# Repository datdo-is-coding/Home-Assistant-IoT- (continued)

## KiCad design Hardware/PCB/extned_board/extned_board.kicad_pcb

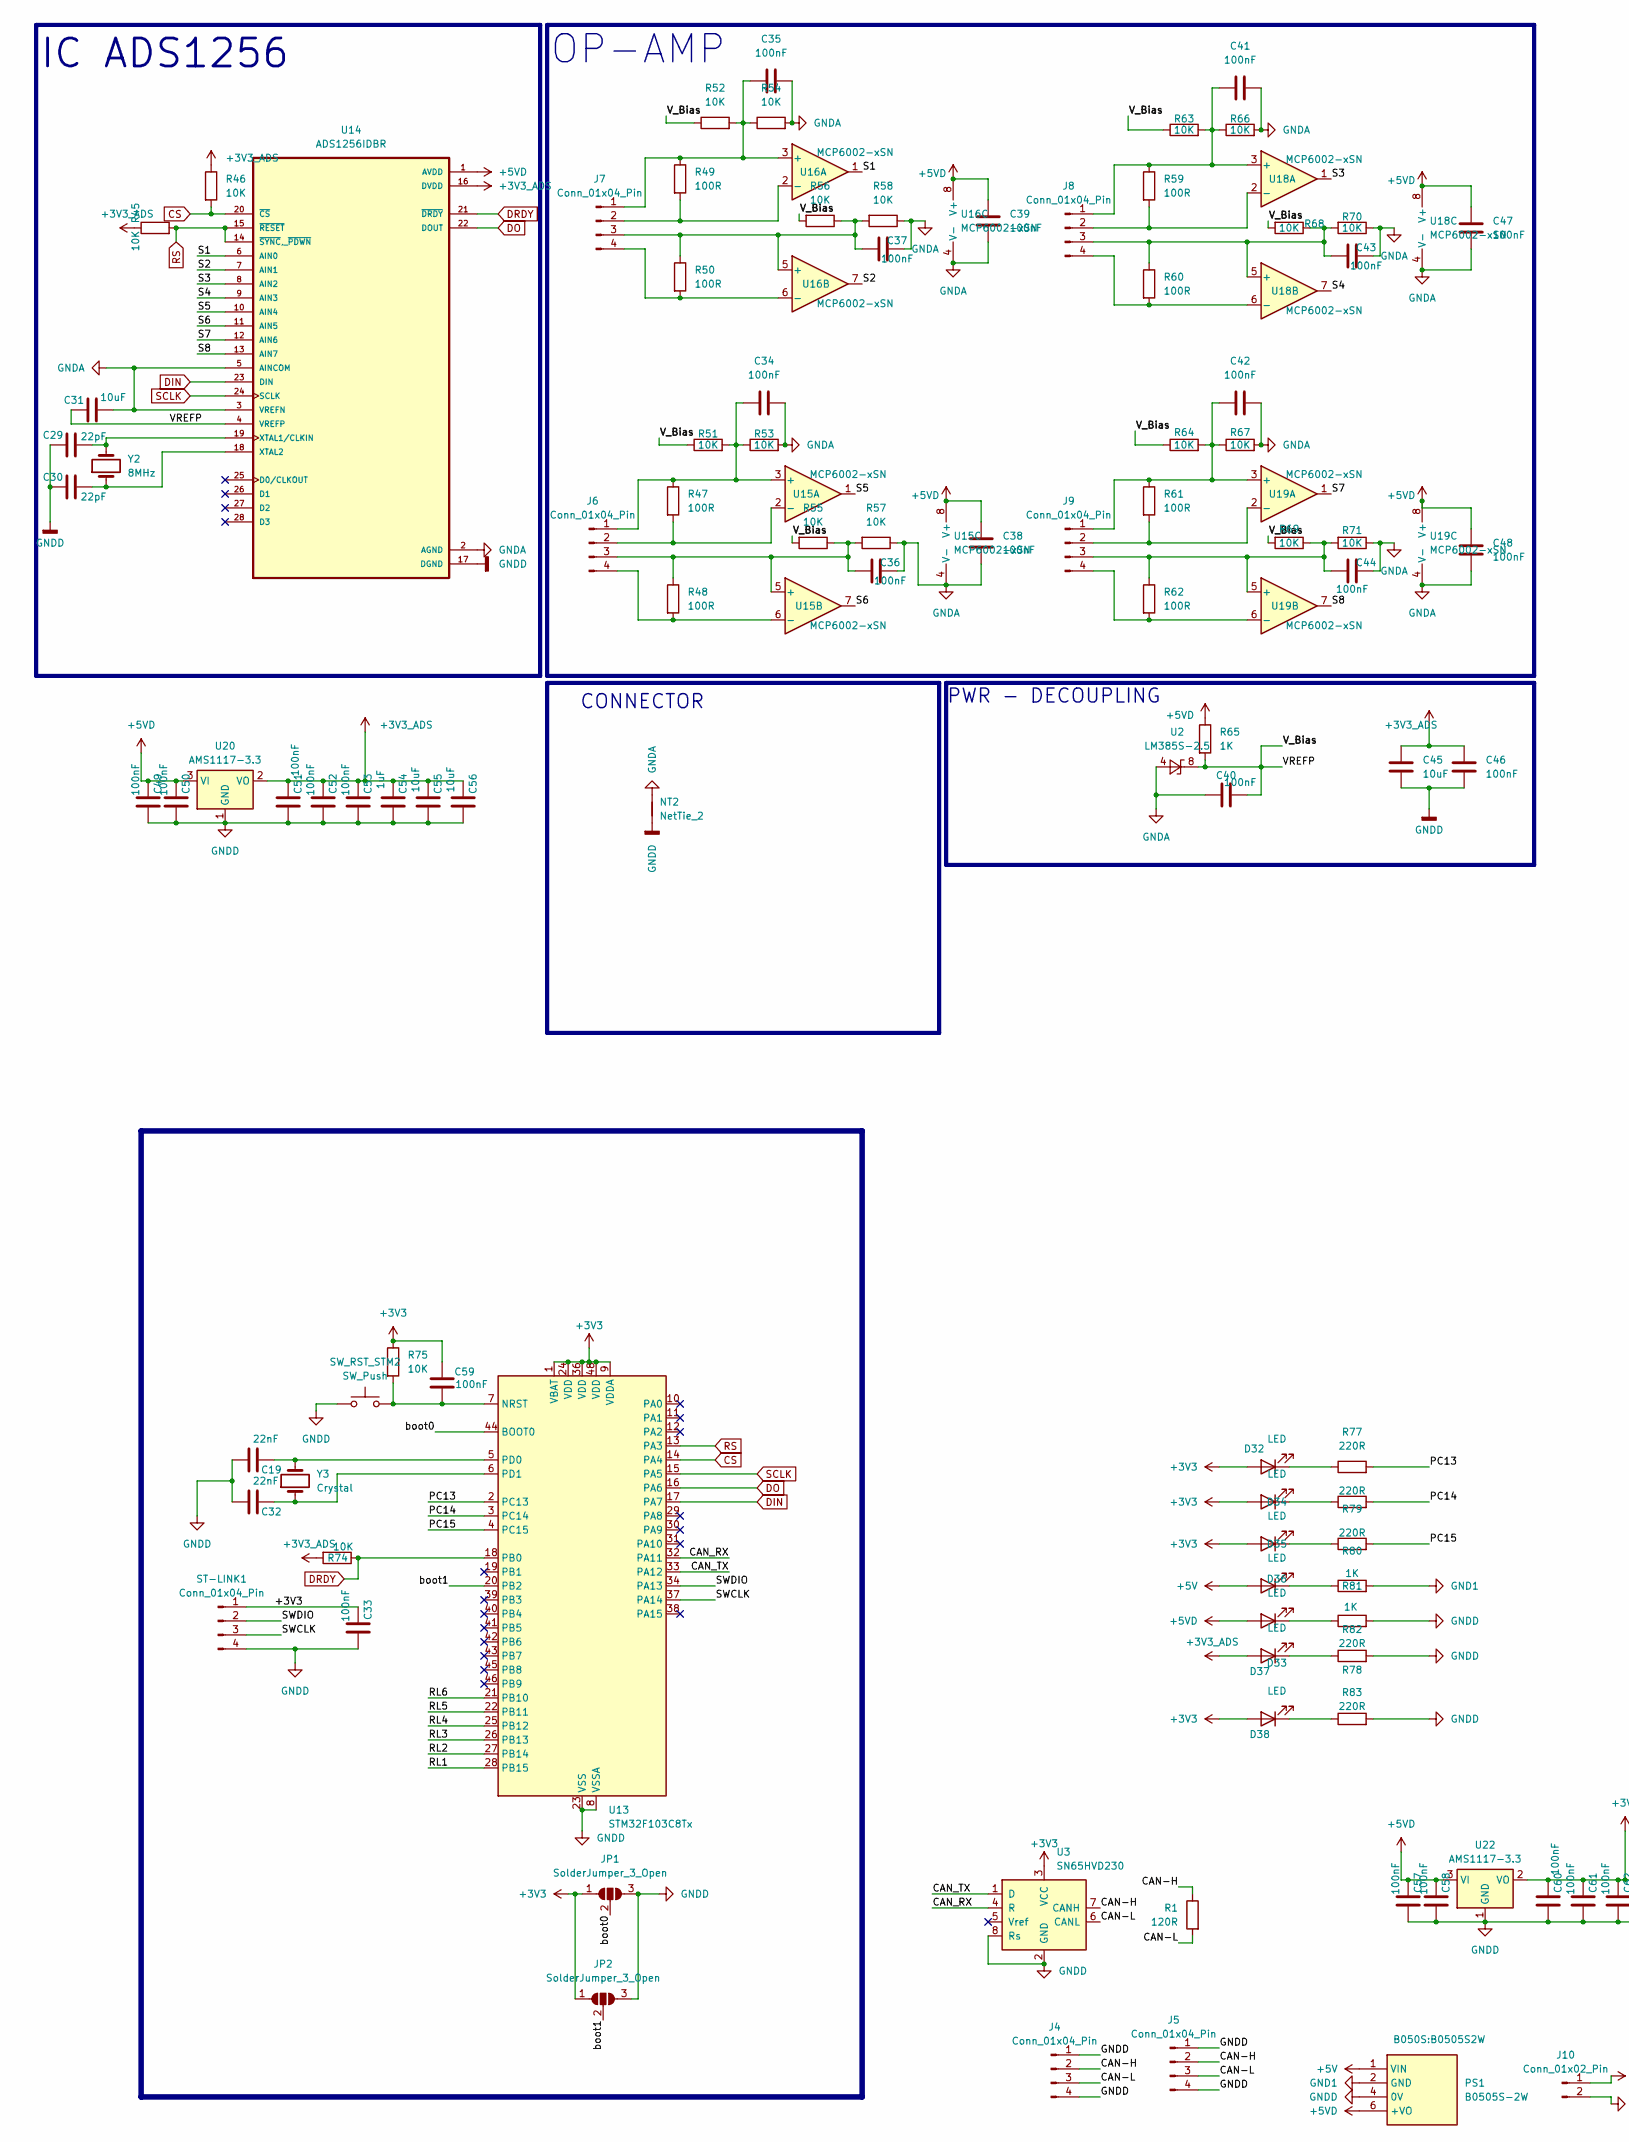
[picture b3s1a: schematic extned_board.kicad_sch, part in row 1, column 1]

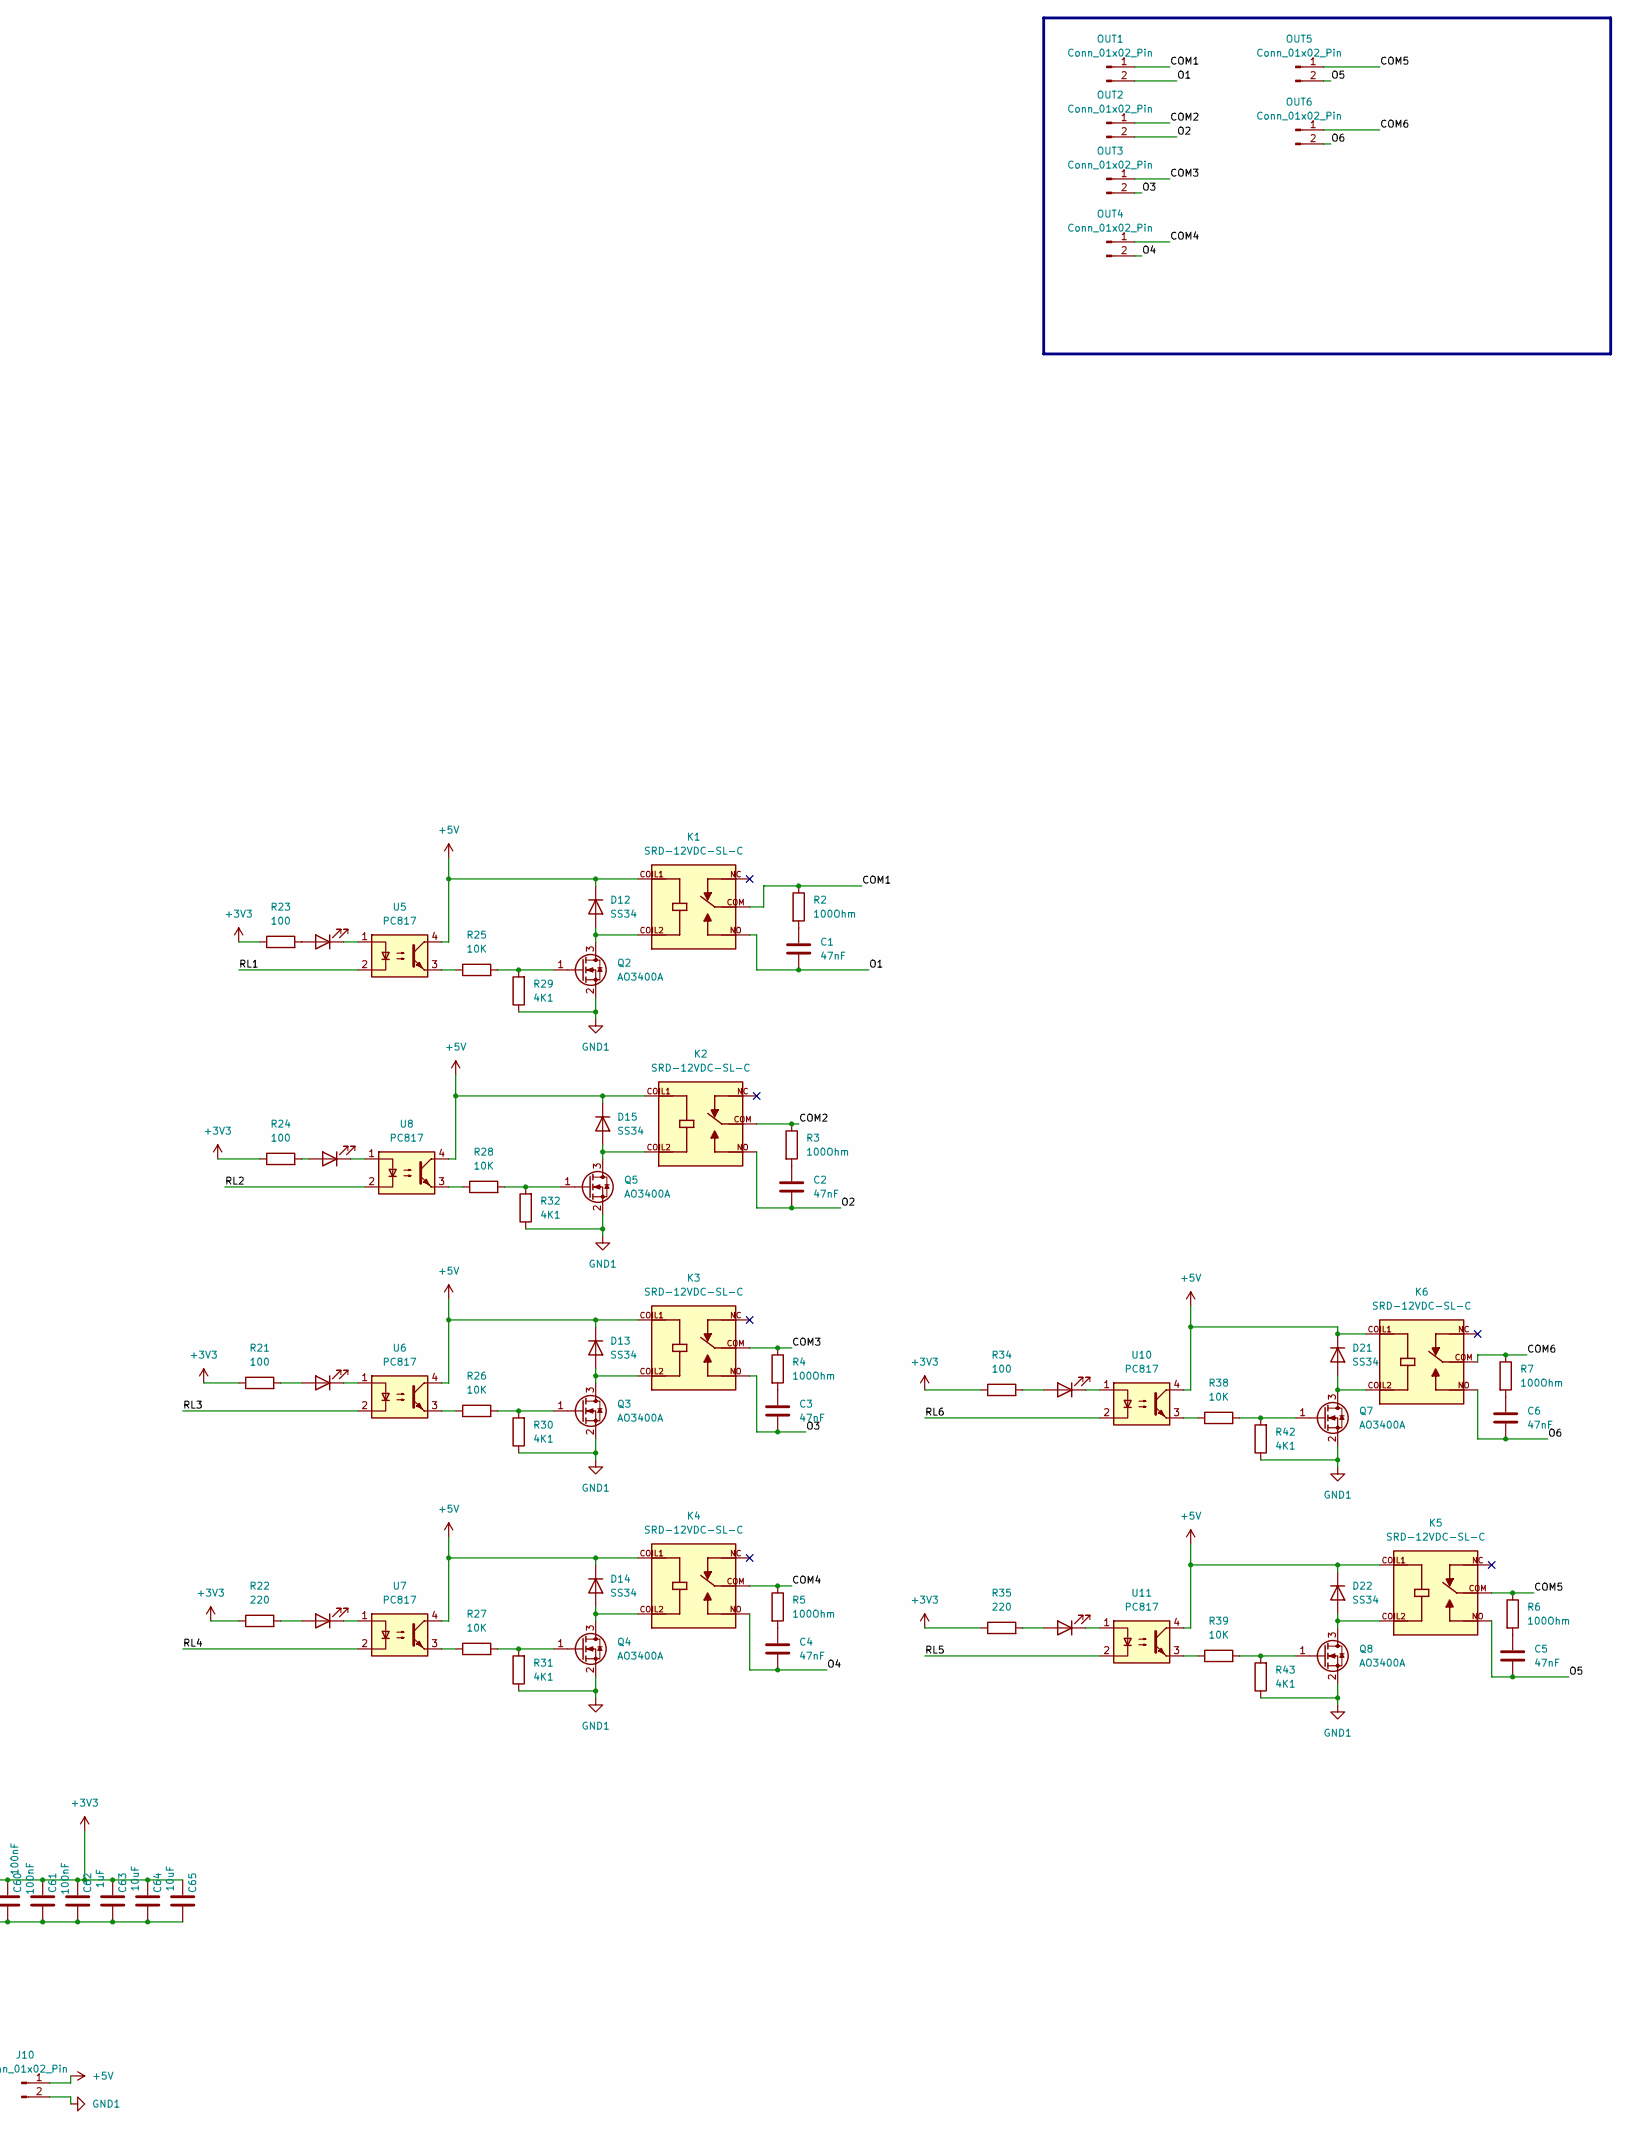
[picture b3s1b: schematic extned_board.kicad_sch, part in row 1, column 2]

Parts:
C1, C2, C3, C4, C5, C6: 47nF; C_Disc_D10.5mm_W5.0mm_P7.50mm
C19, C32: 22nF; R_0805_2012Metric_Pad1.20x1.40mm_HandSolder
C29, C30: 22pF; R_0805_2012Metric_Pad1.20x1.40mm_HandSolder
C31, C45, C55, C56, C64, C65: 10uF; R_0805_2012Metric_Pad1.20x1.40mm_HandSolder
C33, C34, C35, C36, C37, C38, C39, C40, C41, C42, C43, C44, C46, C47, C48, C49, C50, C51, C52, C53, C57, C58, C59, C60, C61, C62: 100nF; R_0805_2012Metric_Pad1.20x1.40mm_HandSolder
C54, C63: 1uF; R_0805_2012Metric_Pad1.20x1.40mm_HandSolder
D8, D9, D10, D11, D17, D18, D32, D33, D34, D35, D36, D37, D38: LED; LED_0805_2012Metric_Pad1.15x1.40mm_HandSolder
D12, D13, D14, D15, D21, D22: SS34; D_SMA_Handsoldering
J4, J5, J6, J7, J8, J9: Conn_01x04_Pin; PinHeader_1x04_P2.54mm_Vertical
J10: Conn_01x02_Pin; PinHeader_1x02_P2.54mm_Vertical
JP1, JP2: SolderJumper_3_Open; SolderJumper-3_P1.3mm_Open_RoundedPad1.0x1.5mm_NumberLabels
K1, K2, K3, K4, K5, K6: SRD-12VDC-SL-C; RELAY_SRD-12VDC-SL-C; PARTREV 1.0
NT2: NetTie_2; NetTie-2_THT_Pad0.3mm
OUT1, OUT2, OUT3, OUT4, OUT5, OUT6: Conn_01x02_Pin; 2P
PS1: B0505S-2W; B0505S2W; Manufacturer_Part_Number B0505S-2W
Q2, Q3, Q4, Q5, Q7, Q8: AO3400A; SOT-23
R1: 120R; R_0805_2012Metric_Pad1.20x1.40mm_HandSolder
R2, R3, R4, R5, R6, R7: 100Ohm; R_Axial_DIN0414_L11.9mm_D4.5mm_P15.24mm_Horizontal
R21, R23, R24, R34: 100; R_0805_2012Metric_Pad1.20x1.40mm_HandSolder
R22, R35: 220; R_0805_2012Metric_Pad1.20x1.40mm_HandSolder
R25, R26, R27, R28, R38, R39, R45, R46, R51, R52, R53, R54, R55, R56, R57, R58, R63, R64, R66, R67, R68, R69, R70, R71, R74, R75: 10K; R_0805_2012Metric_Pad1.20x1.40mm_HandSolder
R29, R30, R31, R32, R42, R43: 4K1; R_0805_2012Metric_Pad1.20x1.40mm_HandSolder
R47, R48, R49, R50, R59, R60, R61, R62: 100R; R_0805_2012Metric_Pad1.20x1.40mm_HandSolder
R65, R80, R81: 1K; R_0805_2012Metric_Pad1.20x1.40mm_HandSolder
R77, R78, R79, R82, R83: 220R; R_0805_2012Metric_Pad1.20x1.40mm_HandSolder
ST-LINK1: Conn_01x04_Pin; PinHeader_1x04_P2.54mm_Vertical
SW_RST_STM2: SW_Push; SW_SPST_FSMSM
U2: LM385S-2.5; SOIC-8_3.9x4.9mm_P1.27mm
U3: SN65HVD230; SOIC-8_3.9x4.9mm_P1.27mm
U5, U6, U7, U8, U10, U11: PC817; DIL04
U13: STM32F103C8Tx; LQFP-48_7x7mm_P0.5mm
U14: ADS1256IDBR; SOP65P780X200-28N
U15, U16, U18, U19: MCP6002-xSN; SOIC8-N_MC_MCH-M
U20, U22: AMS1117-3.3; SOT-223-3_TabPin2
Y2: 8MHz; Resonator-2Pin_W7.0mm_H2.5mm
Y3: Crystal; Resonator-2Pin_W7.0mm_H2.5mm

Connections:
+3V3: C33.2, C59.2, C60.2, C61.2, C62.2, C63.2, C64.2, C65.2, D32.2 (A), D33.2 (A), D34.2 (A), D38.2 (A), JP1.1 (A), JP2.1 (A), R21.1, R22.1, R23.1, R24.1, R34.1, R35.1, R75.1, ST-LINK1.1, U3.3 (VCC), U13.1 (VBAT), U13.9 (VDDA), U13.24 (VDD), U13.36 (VDD), U13.48 (VDD), U22.2 (VO); also elsewhere on the board
+3V3_ADS: C45.1, C46.1, C51.2, C52.2, C53.2, C54.2, C55.2, C56.2, D37.2 (A), R45.1, R46.1, R74.2, U14.16 (DVDD), U20.2 (VO)
+5V: D12.1 (K), D13.1 (K), D14.1 (K), D15.1 (K), D21.1 (K), D22.1 (K), D35.2 (A), J10.1, K1.COIL1, K2.COIL1, K3.COIL1, K4.COIL1, K5.COIL1, K6.COIL1, PS1.1 (VIN), U5.4, U6.4, U7.4, U8.4, U10.4, U11.4
+5VD: C38.1, C39.1, C47.1, C48.1, C49.2, C50.2, C57.2, C58.2, D36.2 (A), PS1.6 (+VO), R65.1, U14.1 (AVDD), U15.8 (V+), U16.8 (V+), U18.8 (V+), U19.8 (V+), U20.3 (VI), U22.3 (VI)
/CAN-H: J4.2, J5.2, R1.1, U3.7 (CANH); also elsewhere on the board
/CAN-L: J4.3, J5.3, R1.2, U3.6 (CANL); also elsewhere on the board
/CAN_RX: U3.4 (R), U13.32 (PA11)
/CAN_TX: U3.1 (D), U13.33 (PA12)
/COM1: K1.COM, OUT1.1, R2.1
/COM2: K2.COM, OUT2.1, R3.1
/COM3: K3.COM, OUT3.1, R4.1
/COM4: K4.COM, OUT4.1, R5.1
/COM5: K5.COM, OUT5.1, R6.1
/COM6: K6.COM, OUT6.1, R7.1
/O1: C1.2, K1.NO, OUT1.2
/O2: C2.2, K2.NO, OUT2.2
/O3: C3.2, K3.NO, OUT3.2
/O4: C4.2, K4.NO, OUT4.2
/O5: C5.2, K5.NO, OUT5.2
/O6: C6.2, K6.NO, OUT6.2
/PC13: R77.2, U13.2 (PC13)
/PC14: R78.2, U13.3 (PC14)
/PC15: R79.2, U13.4 (PC15)
/RL1: U5.2, U13.28 (PB15)
/RL2: U8.2, U13.27 (PB14)
/RL3: U6.2, U13.26 (PB13)
/RL4: U7.2, U13.25 (PB12)
/RL5: U11.2, U13.22 (PB11)
/RL6: U10.2, U13.21 (PB10)
/S1: U14.6 (AIN0), U16.1
/S2: U14.7 (AIN1), U16.7
/S3: U14.8 (AIN2), U18.1
/S4: U14.9 (AIN3), U18.7
/S5: U14.10 (AIN4), U15.1
/S6: U14.11 (AIN5), U15.7
/S7: U14.12 (AIN6), U19.1
/S8: U14.13 (AIN7), U19.7
/SWCLK: ST-LINK1.3, U13.37 (PA14); also elsewhere on the board
/SWDIO: ST-LINK1.2, U13.34 (PA13); also elsewhere on the board
/VREFP: C31.2, C40.1, R51.1, R52.1, R55.2, R56.2, R63.1, R64.1, R65.2, R68.2, R69.2, U2.6 (K), U2.8 (K), U14.4 (VREFP)
/boot0: JP1.2 (C), U13.44 (BOOT0)
/boot1: JP2.2 (C), U13.20 (PB2)
CS: R46.2, U13.14 (PA4), U14.20 (~CS)
DIN: U13.17 (PA7), U14.23 (DIN)
DO: U13.16 (PA6), U14.22 (DOUT)
DRDY: R74.1, U13.18 (PB0), U14.21 (~DRDY)
GND1: J10.2, PS1.2 (GND), Q2.2 (S), Q3.2 (S), Q4.2 (S), Q5.2 (S), Q7.2 (S), Q8.2 (S), R29.1, R30.1, R31.1, R32.1, R42.1, R43.1, R80.2
GNDA: C31.1, C34.2, C35.2, C36.2, C37.2, C38.2, C39.2, C40.2, C41.2, C42.2, C43.2, C44.2, C47.2, C48.2, NT2.2, R53.2, R54.2, R57.1, R58.1, R66.2, R67.2, R70.1, R71.1, U2.4 (A), U14.2 (AGND), U14.3 (VREFN), U14.5 (AINCOM), U15.4 (V-), U16.4 (V-), U18.4 (V-), U19.4 (V-)
GNDD: C19.1, C29.2, C30.2, C32.1, C33.1, C45.2, C46.2, C49.1, C50.1, C51.1, C52.1, C53.1, C54.1, C55.1, C56.1, C57.1, C58.1, C60.1, C61.1, C62.1, C63.1, C64.1, C65.1, JP1.3 (B), JP2.3 (B), NT2.1, PS1.4 (0V), R81.2, R82.2, R83.2, ST-LINK1.4, SW_RST_STM2.1, U3.2 (GND), U3.8 (Rs), U13.8 (VSSA), U13.23 (VSS), U13.35 (VSS), U13.47 (VSS), U14.17 (DGND), U20.1 (GND), U22.1 (GND); also elsewhere on the board
unnamed: C1.1, R2.2
unnamed: C2.1, R3.2
unnamed: C3.1, R4.2
unnamed: C4.1, R5.2
unnamed: C5.1, R6.2
unnamed: C6.1, R7.2
unnamed: D8.2 (A), R23.2
unnamed: D8.1 (K), U5.1
unnamed: D9.2 (A), R21.2
unnamed: D9.1 (K), U6.1
unnamed: D10.2 (A), R22.2
unnamed: D10.1 (K), U7.1
unnamed: D11.2 (A), R24.2
unnamed: D11.1 (K), U8.1
unnamed: D12.2 (A), K1.COIL2, Q2.3 (D)
unnamed: D13.2 (A), K3.COIL2, Q3.3 (D)
unnamed: D14.2 (A), K4.COIL2, Q4.3 (D)
unnamed: D15.2 (A), K2.COIL2, Q5.3 (D)
unnamed: D17.2 (A), R34.2
unnamed: D17.1 (K), U10.1
unnamed: D18.2 (A), R35.2
unnamed: D18.1 (K), U11.1
unnamed: D21.2 (A), K6.COIL2, Q7.3 (D)
unnamed: D22.2 (A), K5.COIL2, Q8.3 (D)
unnamed: D32.1 (K), R77.1
unnamed: D33.1 (K), R78.1
unnamed: D34.1 (K), R79.1
unnamed: D35.1 (K), R80.1
unnamed: D36.1 (K), R81.1
unnamed: D37.1 (K), R82.1
unnamed: D38.1 (K), R83.1
unnamed: J4.1, J4.4, J5.1, J5.4
unnamed: C34.1, J6.1, R47.1, R51.2, R53.1, U15.3 (+)
unnamed: J6.2, R47.2, U15.2 (-)
unnamed: C36.1, J6.3, R48.1, R55.1, R57.2, U15.5 (+)
unnamed: J6.4, R48.2, U15.6 (-)
unnamed: C35.1, J7.1, R49.1, R52.2, R54.1, U16.3 (+)
unnamed: J7.2, R49.2, U16.2 (-)
unnamed: C37.1, J7.3, R50.1, R56.1, R58.2, U16.5 (+)
unnamed: J7.4, R50.2, U16.6 (-)
unnamed: C41.1, J8.1, R59.1, R63.2, R66.1, U18.3 (+)
unnamed: J8.2, R59.2, U18.2 (-)
unnamed: C43.1, J8.3, R60.1, R68.1, R70.2, U18.5 (+)
unnamed: J8.4, R60.2, U18.6 (-)
unnamed: C42.1, J9.1, R61.1, R64.2, R67.1, U19.3 (+)
unnamed: J9.2, R61.2, U19.2 (-)
unnamed: C44.1, J9.3, R62.1, R69.1, R71.2, U19.5 (+)
unnamed: J9.4, R62.2, U19.6 (-)
unnamed: Q2.1 (G), R25.2, R29.2
unnamed: Q3.1 (G), R26.2, R30.2
unnamed: Q4.1 (G), R27.2, R31.2
unnamed: Q5.1 (G), R28.2, R32.2
unnamed: Q7.1 (G), R38.2, R42.2
unnamed: Q8.1 (G), R39.2, R43.2
unnamed: R25.1, U5.3
unnamed: R26.1, U6.3
unnamed: R27.1, U7.3
unnamed: R28.1, U8.3
unnamed: R38.1, U10.3
unnamed: R39.1, U11.3
unnamed 109: C59.1, R75.2, SW_RST_STM2.2, U13.7 (NRST); also elsewhere on the board
unnamed: C19.2, U13.5 (PD0), Y3.2
unnamed: C32.2, U13.6 (PD1), Y3.1
unnamed: C29.1, U14.19 (XTAL1/CLKIN), Y2.2
unnamed: C30.1, U14.18 (XTAL2), Y2.1
RS: R45.2, U13.13 (PA3), U14.14 (~SYNC,_~PDWN), U14.15 (~RESET)
SCLK: U13.15 (PA5), U14.24 (SCLK)

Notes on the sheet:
PWR - DECOUPLING
OP-AMP
IC ADS1256
CONNECTOR

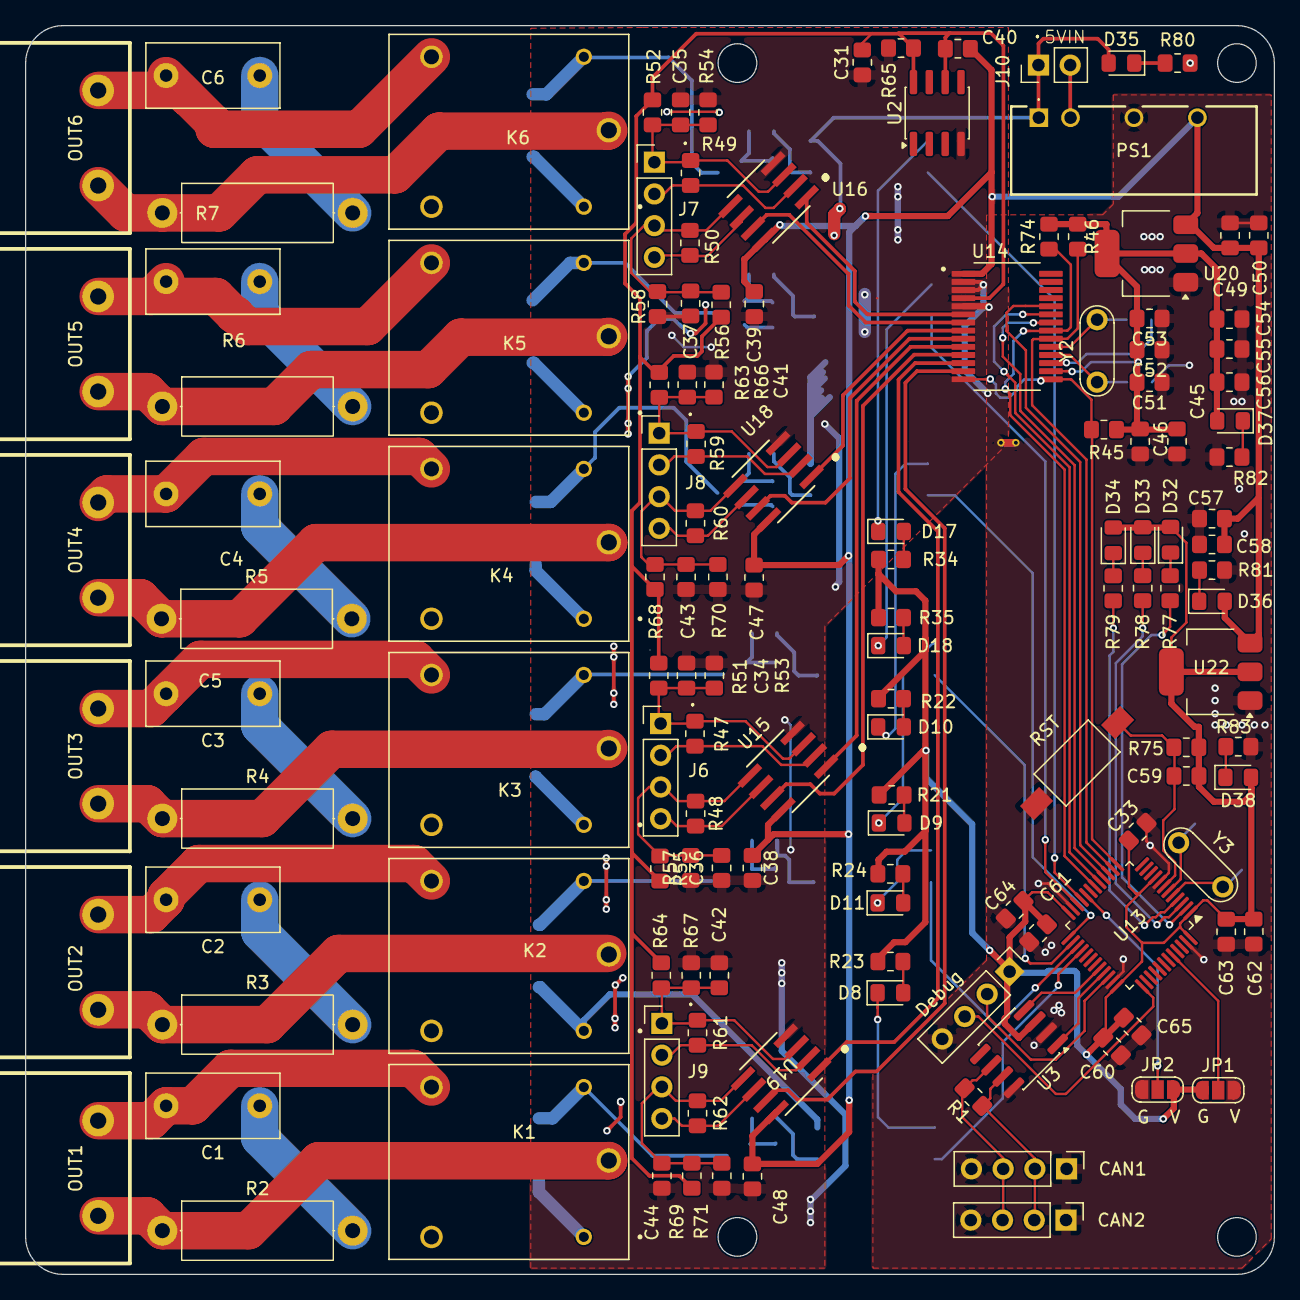
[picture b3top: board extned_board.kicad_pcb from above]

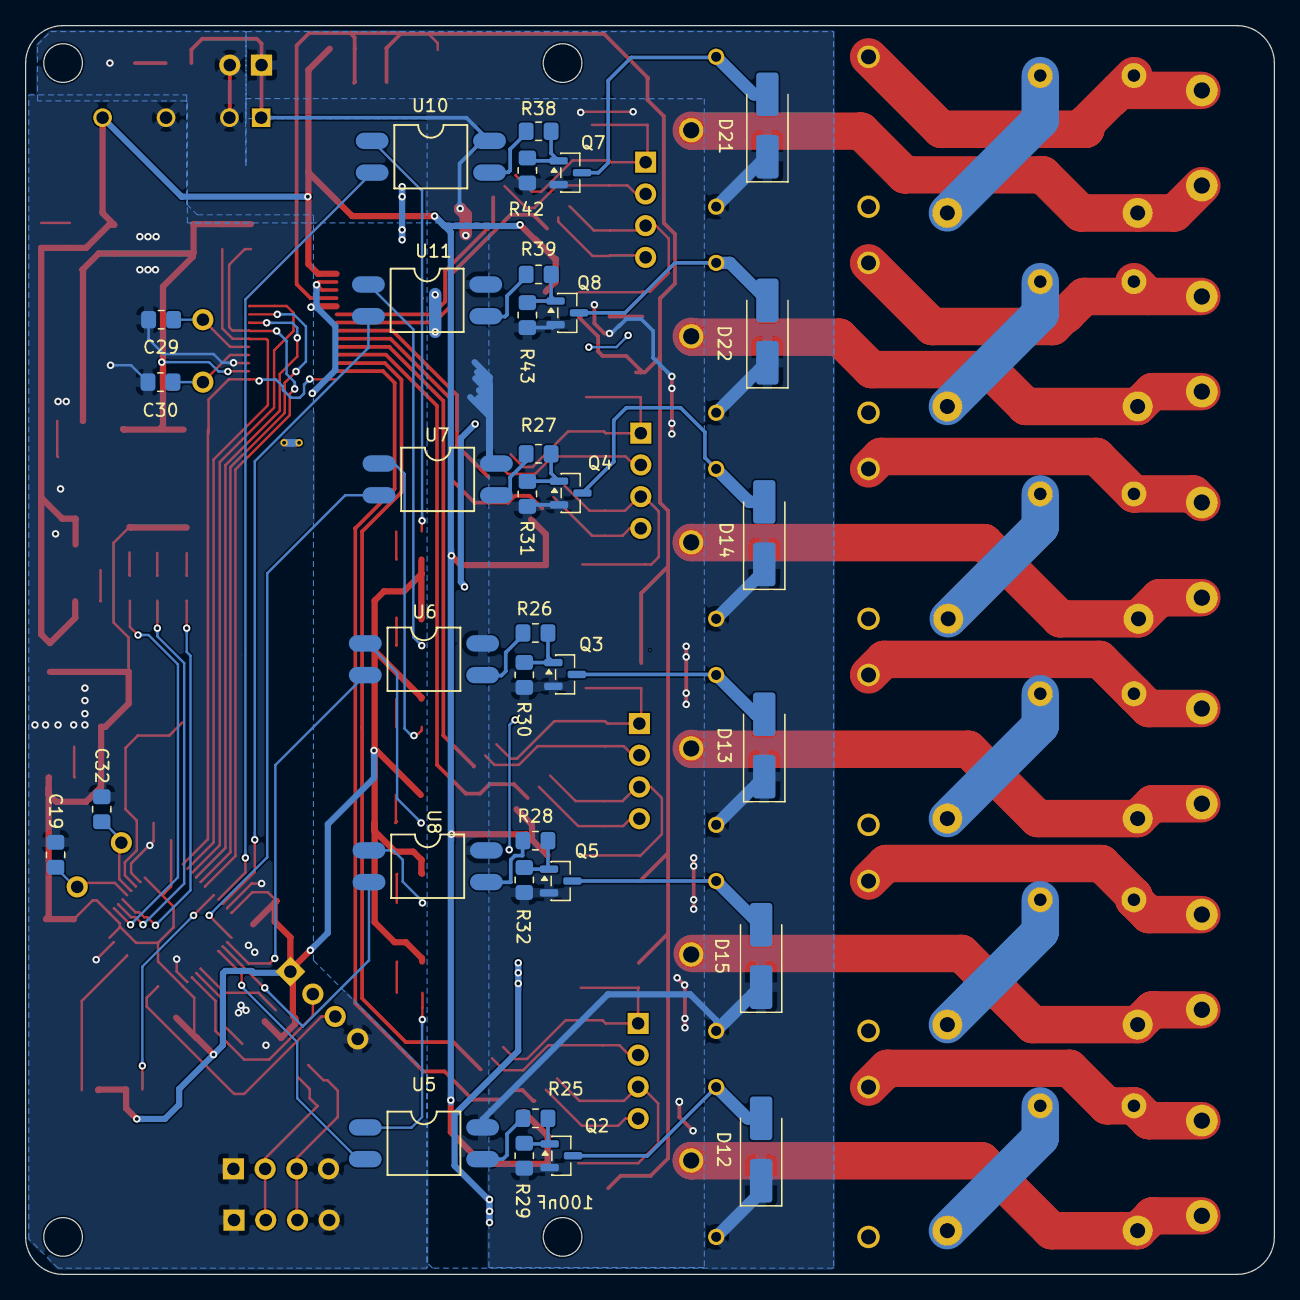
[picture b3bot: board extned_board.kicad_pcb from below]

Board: 2 copper layers, 100.0 x 100.0 mm, 173 parts (34 on the bottom side), 115 nets.

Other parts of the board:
CAN1, CAN2: Conn_01x04_Pin; PinHeader_1x04_P2.54mm_Vertical
Debug: Conn_01x04_Pin; PinHeader_1x04_P2.54mm_Vertical
RST: SW_Push; SW_SPST_FSMSM

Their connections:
+3V3: Debug.1; also elsewhere on the board
/CAN-H: CAN1.2, CAN2.2; also elsewhere on the board
/CAN-L: CAN1.3, CAN2.3; also elsewhere on the board
/SWCLK: Debug.3; also elsewhere on the board
/SWDIO: Debug.2; also elsewhere on the board
GNDD: CAN1.1, CAN1.4, CAN2.1, CAN2.4, Debug.4, RST.1; also elsewhere on the board
unnamed 109: RST.2; also elsewhere on the board

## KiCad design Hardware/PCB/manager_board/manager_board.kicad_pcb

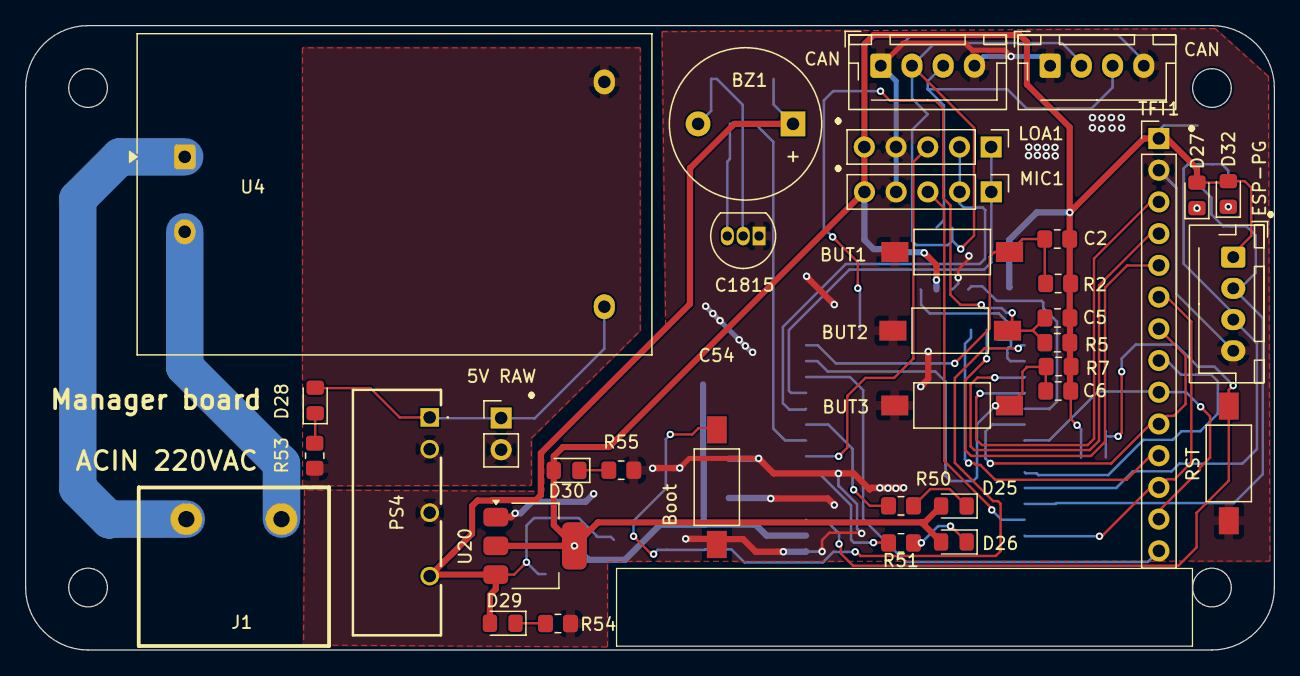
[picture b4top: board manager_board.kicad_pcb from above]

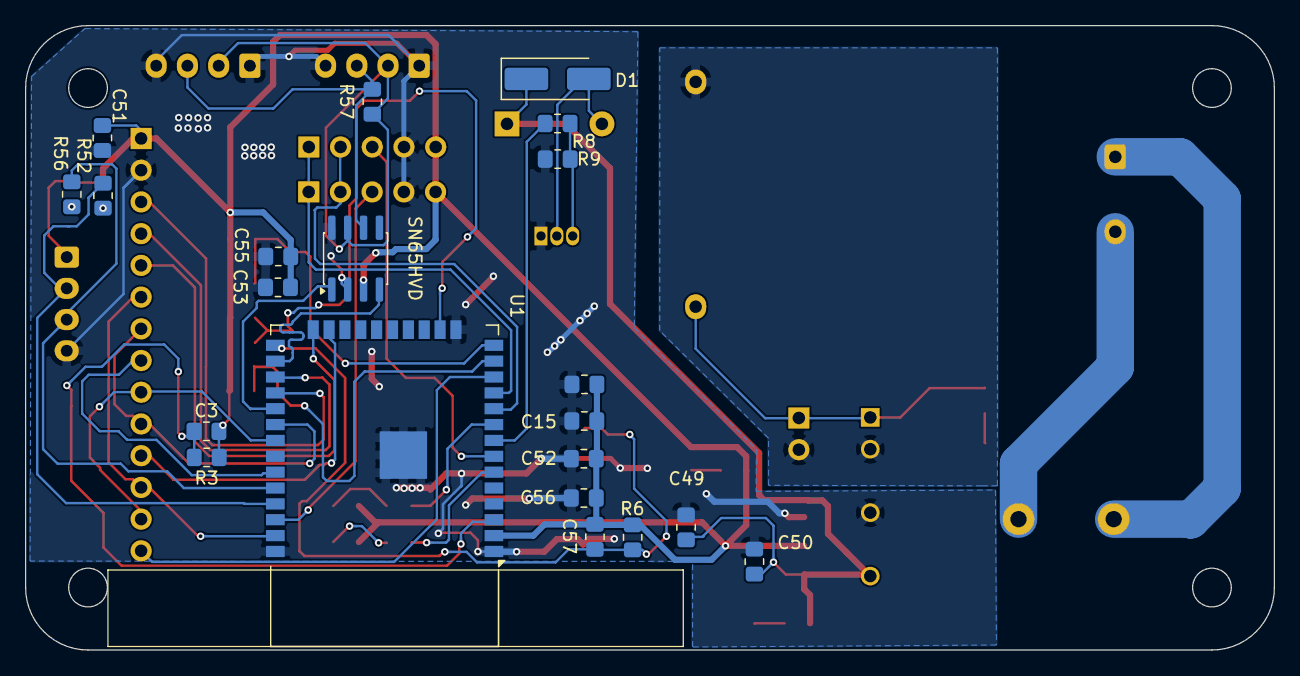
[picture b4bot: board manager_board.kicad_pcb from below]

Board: 2 copper layers, 100.0 x 50.0 mm, 57 parts (21 on the bottom side), 43 nets.

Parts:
5V RAW: Conn_01x02_Pin; PinHeader_1x02_P2.54mm_Vertical
BUT1, BUT2, BUT3: SW_Push; SW_SPST_FSMSM
BZ1: Buzzer; Buzzer_12x9.5RM7.6
Boot: SW_Push; SW_SPST_FSMSM
C2, C3, C5, C6, C49, C50, C51, C52, C53, C57: 100nF; R_0805_2012Metric_Pad1.20x1.40mm_HandSolder
C15, C55, C56: 10uF; R_0805_2012Metric_Pad1.20x1.40mm_HandSolder
C54: 1uF; R_0805_2012Metric_Pad1.20x1.40mm_HandSolder
C1815: 2SC1815; TO-92_Inline
CAN: Conn_01x04_Pin; JST_XH_B4B-XH-AM_1x04_P2.50mm_Vertical
CAN#2: Conn_01x04_Pin; JST_XH_B4B-XH-AM_1x04_P2.50mm_Vertical
D1: 1N4007; D_SMA_Handsoldering
D25, D26, D27, D28, D29, D30, D32: LED; LED_0805_2012Metric_Pad1.15x1.40mm_HandSolder
ESP-PG: Conn_01x04_Pin; JST_XH_B4B-XH-AM_1x04_P2.50mm_Vertical
J1: KF7.62-2P; 2P
LOA1: Conn_01x05_Pin; PinHeader_1x05_P2.54mm_Vertical
MIC1: Conn_01x05_Pin; PinHeader_1x05_P2.54mm_Vertical
PS4: B0505S-2W; B0505S2W
R2, R3, R5, R6, R7, R9: 10K; R_0805_2012Metric_Pad1.20x1.40mm_HandSolder
R8, R52, R53, R54, R56: 1K; R_0805_2012Metric_Pad1.20x1.40mm_HandSolder
R50, R51, R55: 220R; R_0805_2012Metric_Pad1.20x1.40mm_HandSolder
R57: 120R; R_0805_2012Metric_Pad1.20x1.40mm_HandSolder
RST: SW_Push; SW_SPST_FSMSM
SN65HVD: SN65HVD230; SOIC-8_3.9x4.9mm_P1.27mm
TFT1: Conn_01x14_Pin; PinHeader_1x14_P2.54mm_Vertical
U1: ESP32-WROOM-32D
U4: HLK-5M05; Converter_ACDC_Hi-Link_HLK-5Mxx
U20: AMS1117-3.3; SOT-223-3_TabPin2

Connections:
+3V3_ESP: C2.2, C3.2, C5.2, C6.2, C15.2, C51.2, C52.2, C53.2, C54.2, C55.2, C56.2, C57.2, D25.2 (A), D26.2 (A), D27.2 (A), D30.2 (A), D32.2 (A), ESP-PG.1, LOA1.5, MIC1.5, R2.1, R3.1, R5.1, R6.1, R7.1, SN65HVD.3 (VCC), TFT1.1, U1.2 (VDD), U20.2 (VO)
+5V: 5V RAW.1, D28.2 (A), PS4.1 (VIN), U4.4 (+Vout)
+5VD1: BZ1.1 (+), C49.2, C50.2, D1.1 (K), D29.2 (A), PS4.6 (+VO), U20.3 (VI)
/BUT1: BUT1.2, C2.1, R2.2, U1.14 (IO12)
/BUT2: BUT2.2, C5.1, R5.2, U1.16 (IO13)
/BUT3: BUT3.2, C6.1, R7.2, U1.13 (IO14)
/CAN-H: CAN.2, CAN#2.2, R57.2, SN65HVD.7 (CANH)
/CAN-L: CAN.3, CAN#2.3, R57.1, SN65HVD.6 (CANL)
/CAN_RX: SN65HVD.4 (R), U1.26 (IO4)
/CAN_TX: SN65HVD.1 (D), U1.29 (IO5)
/I2S_BCLK: LOA1.1, MIC1.1, U1.11 (IO26)
/I2S_DIN: LOA1.3, U1.7 (IO35)
/I2S_DOUT: MIC1.3, U1.36 (IO22)
/I2S_WS: LOA1.2, MIC1.2, U1.10 (IO25)
/LED1: R50.2, U1.9 (IO33)
/LED2: R51.2, U1.6 (IO34)
/RX0: ESP-PG.3, R56.2, U1.34 (RXD0/IO3)
/TFT_CS: TFT1.3, U1.28 (IO17)
/TFT_DC: TFT1.5, U1.24 (IO2)
/TFT_LED: TFT1.8, U1.33 (IO21)
/TFT_MISO: TFT1.9, TFT1.13, U1.31 (IO19)
/TFT_MOSI: TFT1.6, TFT1.12, U1.37 (IO23)
/TFT_RS: TFT1.4, U1.27 (IO16)
/TFT_SCK: TFT1.7, TFT1.10, U1.30 (IO18)
/TO_CS: TFT1.11, U1.23 (IO15)
/TO_IRQ: TFT1.14, U1.12 (IO27)
/TX0: ESP-PG.2, R52.2, U1.35 (TXD0/IO1)
/buzz: R8.1, U1.8 (IO32)
GND1: 5V RAW.2, PS4.2 (GND), R53.2, U4.3 (-Vout)
GNDD: BUT1.1, BUT2.1, BUT3.1, Boot.2, C15.1, C49.1, C50.1, C51.1, C52.1, C53.1, C54.1, C55.1, C56.1, C1815.1 (E), CAN.1, CAN.4, CAN#2.1, CAN#2.4, ESP-PG.4, LOA1.4, MIC1.4, PS4.4 (0V), R9.2, R54.2, R55.2, RST.1, SN65HVD.2 (GND), SN65HVD.8 (Rs), TFT1.2, U1.1 (GND), U1.15 (GND), U1.38 (GND), U1.39 (GND), U20.1 (GND)
unnamed: BZ1.2 (-), C1815.2 (C), D1.2 (A)
unnamed: D25.1 (K), R50.1
unnamed: D26.1 (K), R51.1
unnamed: D27.1 (K), R52.1
unnamed: D28.1 (K), R53.1
unnamed: D29.1 (K), R54.1
unnamed: D30.1 (K), R55.1
unnamed: D32.1 (K), R56.1
unnamed: C1815.3 (B), R8.2, R9.1
unnamed: C3.1, R3.2, RST.2, U1.3 (EN)
unnamed: Boot.1, C57.1, R6.2, U1.25 (IO0)
unnamed: J1.2, U4.1 (AC/L)
unnamed: J1.1, U4.2 (AC/N)

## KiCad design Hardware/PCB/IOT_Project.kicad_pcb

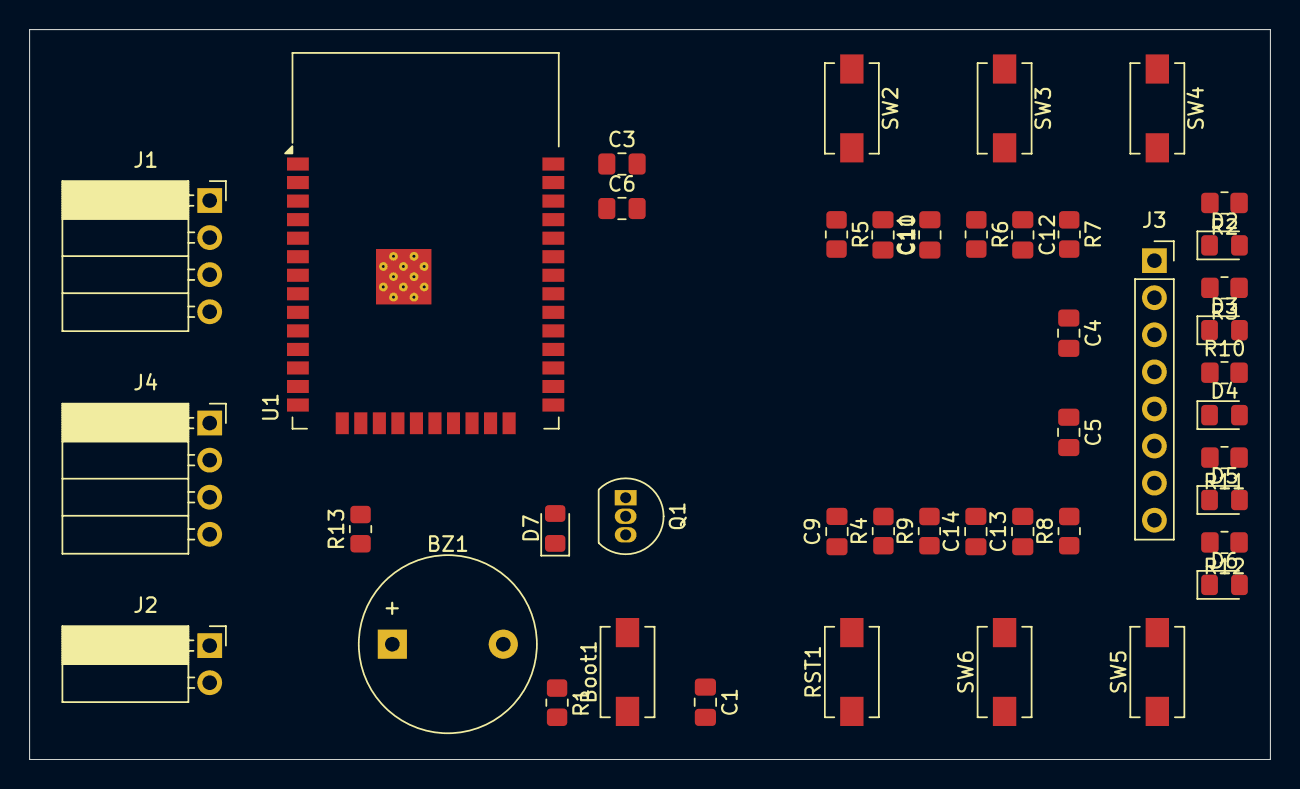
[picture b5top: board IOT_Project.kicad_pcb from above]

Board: 2 copper layers, 85.0 x 50.0 mm, 44 parts (0 on the bottom side), 31 nets, no tracks yet.

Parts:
BZ1: Buzzer; Buzzer_12x9.5RM7.6
Boot1: SW_Push; SW_SPST_EVQPE1
C1, C3, C4, C5, C6, C9, C10, C11, C12, C13, C14: 100nF; C_0805_2012Metric_Pad1.18x1.45mm_HandSolder
D2, D3, D4, D5, D6: LED; LED_0805_2012Metric_Pad1.15x1.40mm_HandSolder
D7: D; D_0805_2012Metric_Pad1.15x1.40mm_HandSolder
J1: Conn_01x04_Pin; PinSocket_1x04_P2.54mm_Horizontal
J2: POWER IN 3V3; PinSocket_1x02_P2.54mm_Horizontal
J3: TFT_2.4; PinSocket_1x08_P2.54mm_Vertical
J4: Program; PinSocket_1x04_P2.54mm_Horizontal
Q1: 2SC1815; TO-92_Inline
R1, R4, R5, R6, R7, R8, R9: 10K; R_0805_2012Metric_Pad1.20x1.40mm_HandSolder
R2, R3, R10, R11, R12: 330R; R_0805_2012Metric_Pad1.20x1.40mm_HandSolder
R13: 1K; R_0805_2012Metric_Pad1.20x1.40mm_HandSolder
RST1: SW_Push; SW_SPST_EVQPE1
SW2, SW3, SW4, SW5, SW6: SW_Push; SW_SPST_EVQPE1
U1: ESP32-WROOM-32D

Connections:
+3.3V: BZ1.1 (+), C3.1, C4.1, C5.1, C6.1, D7.1 (K), J1.1, J2.1, J3.1, J4.1, R1.2, R2.2, R3.2, R4.2, R5.2, R6.2, R7.2, R8.2, R9.2, R10.2, R11.2, R12.2, U1.2 (VDD)
BL: J3.8, U1.8 (IO32)
BOOT: Boot1.2, C1.1, R1.1, U1.25 (IO0)
BUT1: C10.1, R5.1, SW2.2, U1.9 (IO33)
BUT2: C11.1, R6.1, SW3.2, U1.6 (IO34)
BUT3: C12.1, R7.1, SW4.2, U1.7 (IO35)
BUT4: C13.1, R8.1, SW5.2, U1.4 (SENSOR_VP)
BUT5: C14.1, R9.1, SW6.2, U1.5 (SENSOR_VN)
Buzz: R13.2, U1.16 (IO13)
CLK: J3.7, U1.30 (IO18)
CS: J3.3, U1.29 (IO5)
DC: J3.5, U1.26 (IO4)
GND: Boot1.1, C1.2, C3.2, C4.2, C5.2, C6.2, C9.2, C10.2, C11.2, C12.2, C13.2, C14.2, D2.1 (K), J1.4, J2.2, J3.2, J4.4, Q1.1 (E), RST1.1, SW2.1, SW3.1, SW4.1, SW5.1, SW6.1, U1.1 (GND), U1.15 (GND), U1.38 (GND), U1.39 (GND)
Led_BLE: D4.1 (K), U1.11 (IO26)
Led_ERR: D5.1 (K), U1.12 (IO27)
Led_RUN: D6.1 (K), U1.13 (IO14)
Led_WF: D3.1 (K), U1.10 (IO25)
MOSI: J3.6, U1.37 (IO23)
unnamed: BZ1.2 (-), D7.2 (A), Q1.2 (C)
unnamed: D2.2 (A), R2.1
unnamed: D3.2 (A), R3.1
unnamed: D4.2 (A), R10.1
unnamed: D5.2 (A), R11.1
unnamed: D6.2 (A), R12.1
unnamed: Q1.3 (B), R13.1
RST: J3.4, U1.23 (IO15)
RST_BUT: C9.1, R4.1, RST1.2, U1.3 (EN)
RX: J1.3, U1.28 (IO17)
RX0: J4.3, U1.35 (TXD0/IO1)
TX: J1.2, U1.27 (IO16)
TX0: J4.2, U1.34 (RXD0/IO3)
